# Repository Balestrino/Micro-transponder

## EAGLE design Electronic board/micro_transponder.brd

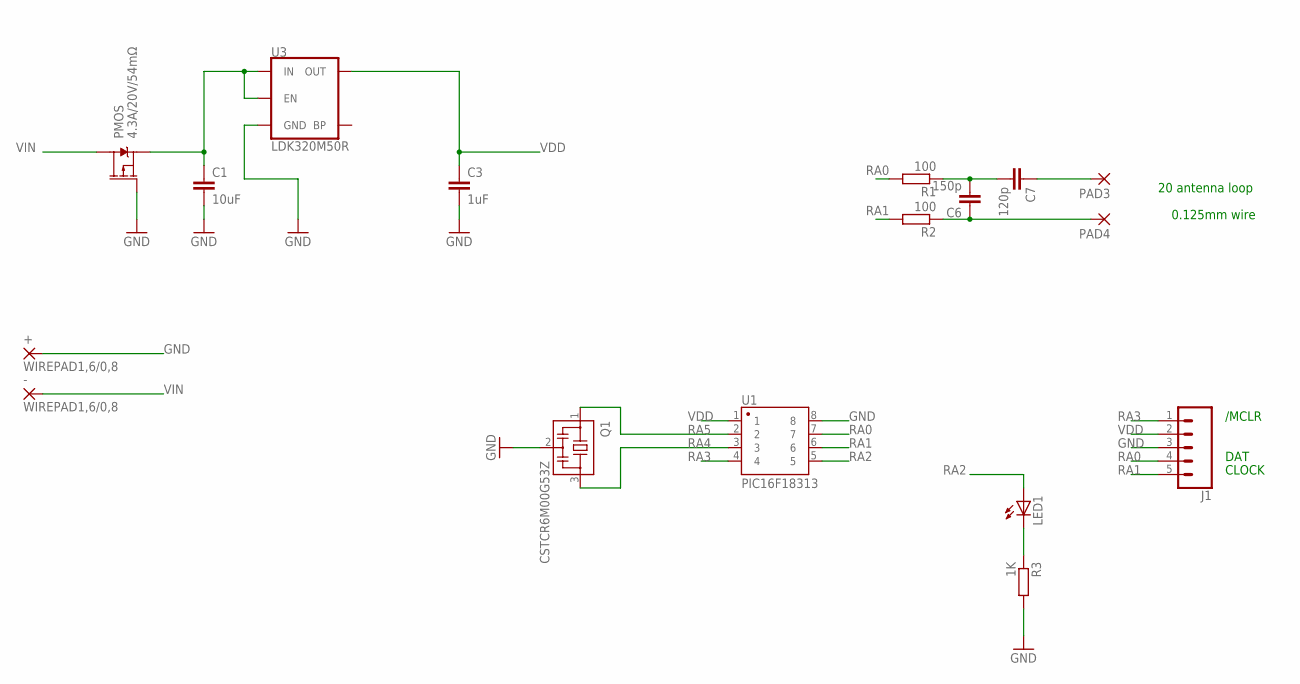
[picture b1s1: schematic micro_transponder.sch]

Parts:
+: WIREPAD1,6/0,8; 1,6/0,8
-: WIREPAD1,6/0,8; 1,6/0,8
C1: 10uF; C0805
C3: 1uF; C0603
C6: 150p; C0603
C7: 120p; C0603
J1: CONN_051.27MM; 1X05_1.27MM
LED1: LEDCHIP-LED0805; CHIP-LED0805
PAD3, PAD4: 1,6/0,9
PMOS: 4.3A/20V/54mΩ; SOT23-3
Q1: CSTCR6M00G53Z; CSTCR6M
R1, R2: 100; R0603
R3: 1K; R0603
U1: PIC16F18313; SOIC8
U3: LDK320M50R; SOT23-5

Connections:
GND: +.1, C1.2, C3.2, J1.3, PMOS.1 (G), Q1.2, R3.2, U1.8, U3.2 (GND)
unnamed: C1.1, PMOS.2 (S), U3.1 (IN), U3.3 (EN)
unnamed: C6.2, C7.2, R1.1
unnamed: C6.1, PAD4.1, R2.1
unnamed: LED1.C, R3.1
unnamed: C7.1, PAD3.1
RA0: J1.4, R1.2, U1.7
RA1: J1.5, R2.2, U1.6
RA2: LED1.A, U1.5
RA3: J1.1, U1.4
RA4: Q1.3, U1.3
RA5: Q1.1, U1.2
VDD: C3.1, J1.2, U1.1, U3.5 (OUT)
VIN: -.1, PMOS.3 (D)

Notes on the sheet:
/MCLR
DAT
CLOCK
20 antenna loop
0.125mm wire

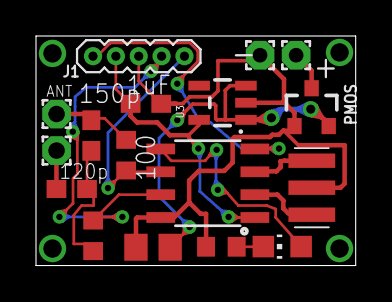
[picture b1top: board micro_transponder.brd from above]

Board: 2 copper layers, 17.8 x 12.8 mm, 17 parts (0 on the bottom side), 14 nets.

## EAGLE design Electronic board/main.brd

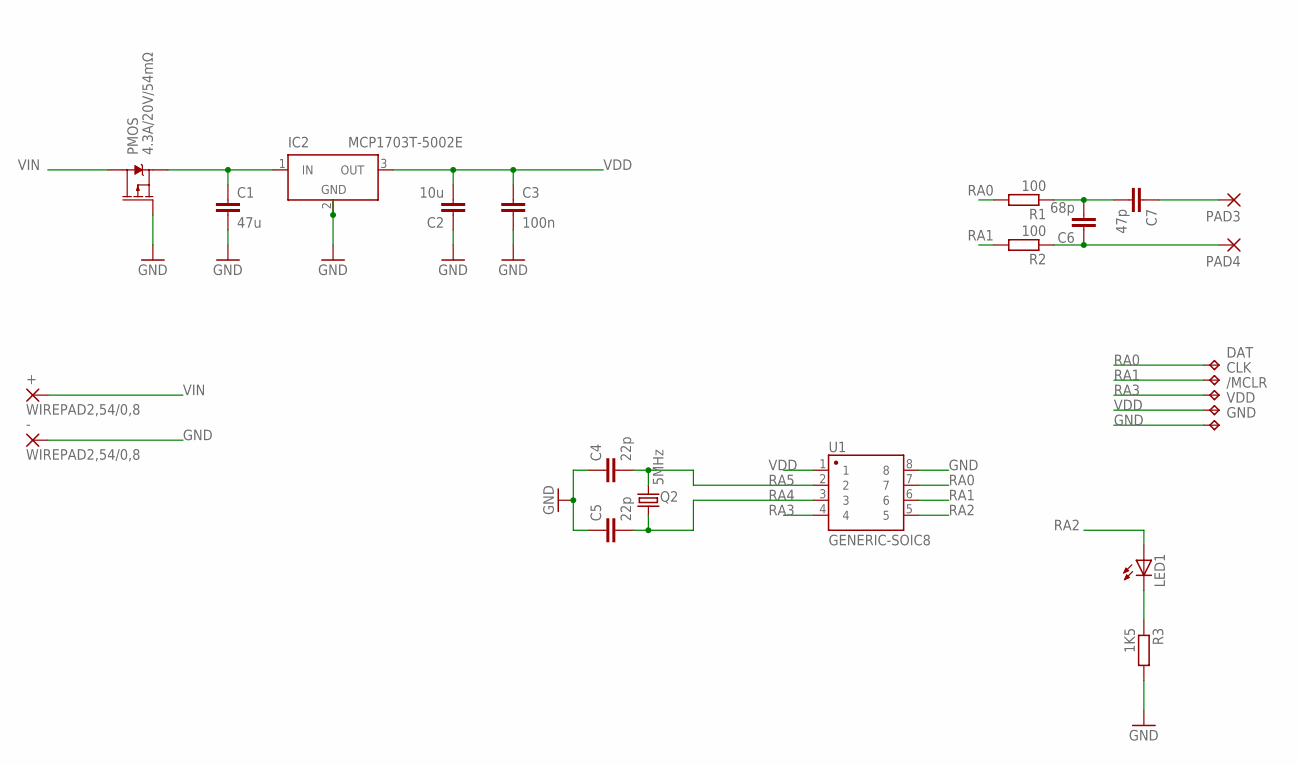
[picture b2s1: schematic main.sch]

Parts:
+: WIREPAD2,54/0,8; 2,54/0,8
-: WIREPAD2,54/0,8; 2,54/0,8
/MCLR: TPTP08SQ; TP08SQ
C1: 47u; C1206
C2: 10u; C1206
C3: 100n; C0603
C4, C5: 22p; C0603
C6: 68p; C0603
C7: 47p; C0603
CLK: TPTP08SQ; TP08SQ
DAT: TPTP08SQ; TP08SQ
GND: TPTP08SQ; TP08SQ
IC2: MCP1703T-5002E; SOT223
LED1: LEDCHIP-LED0603; CHIP-LED0603
PAD3, PAD4: 1,6/0,9
PMOS: 4.3A/20V/54mΩ; SOT23-3
Q2: 5MHz; HC49UP
R1, R2: 100; R0603
R3: 1K5; R0603
U1: GENERIC-SOIC8; SO08-UNIVERSAL
VDD: TPTP08SQ; TP08SQ

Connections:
GND: -.1, C1.2, C2.1, C3.2, C4.1, C5.1, GND.TP, IC2.2 (GND), IC2.4 (GND), PMOS.1 (G), R3.2, U1.8
unnamed: C1.1, IC2.1 (IN), PMOS.2 (S)
unnamed: C6.2, C7.2, R1.1
unnamed: C6.1, PAD4.1, R2.1
unnamed: LED1.C, R3.1
unnamed: C7.1, PAD3.1
RA0: DAT.TP, R1.2, U1.7
RA1: CLK.TP, R2.2, U1.6
RA2: LED1.A, U1.5
RA3: /MCLR.TP, U1.4
RA4: C5.2, Q2.1, U1.3
RA5: C4.2, Q2.2, U1.2
VDD: C2.2, C3.1, IC2.3 (OUT), U1.1, VDD.TP
VIN: +.1, PMOS.3 (D)

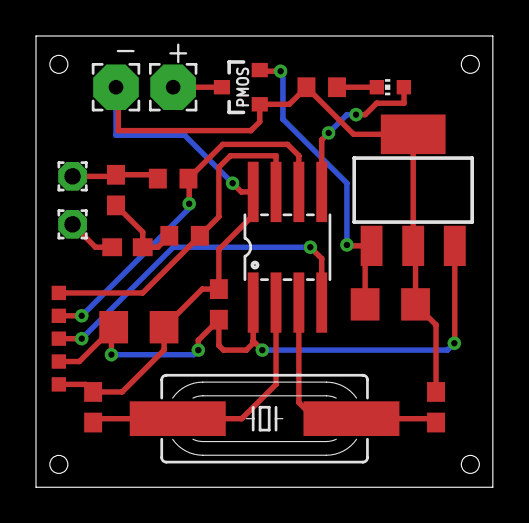
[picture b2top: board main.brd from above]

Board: 2 copper layers, 25.4 x 25.1 mm, 24 parts (0 on the bottom side), 14 nets.

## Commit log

2021-03-31 first upload

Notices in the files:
parts and their libraries:
SparkFun-DiscreteSemi: Licensing: Creative Commons ShareAlike 4.0 International - https://creativecommons.org/licenses/by-sa/4.0
